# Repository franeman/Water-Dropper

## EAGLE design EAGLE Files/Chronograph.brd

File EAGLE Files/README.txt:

The water dropper uses the same board as the chronograph project. Do not install R2 to use the water dropper.
R3 is not needed for the water dropper but will not effect the circuit should you want to use the chronograph.

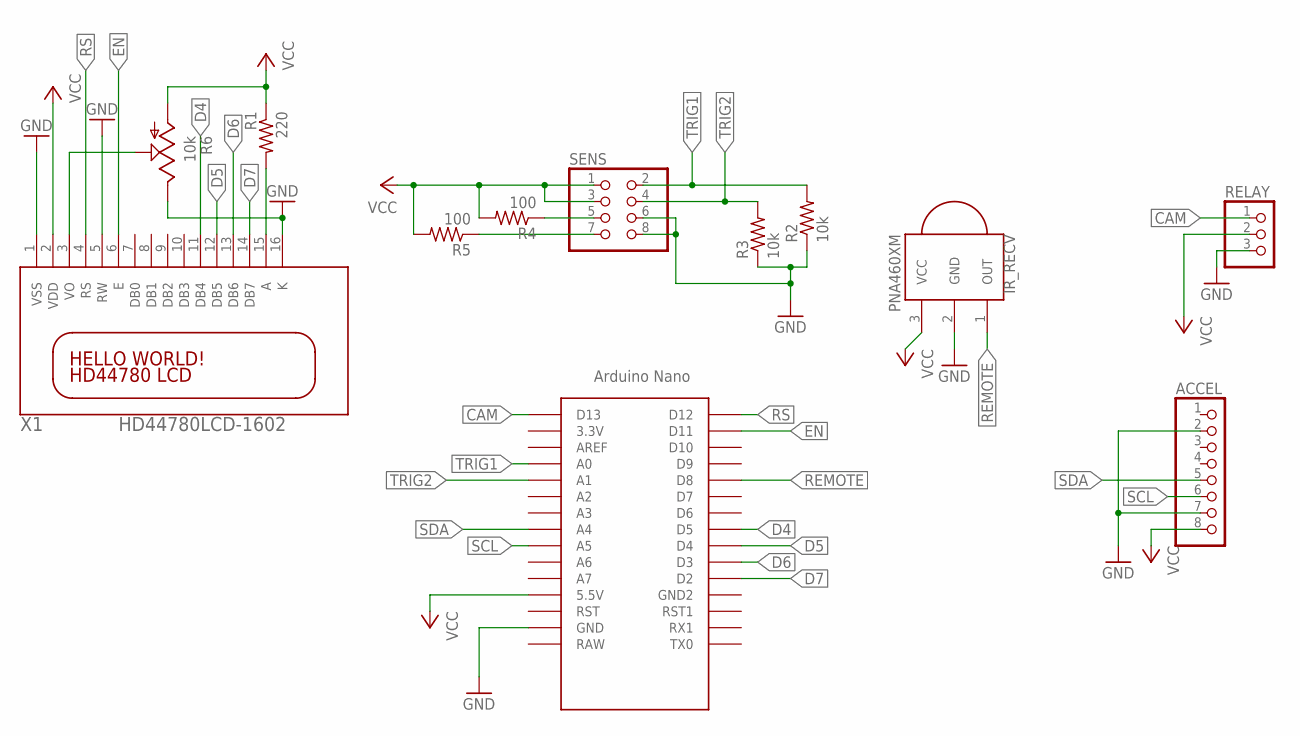
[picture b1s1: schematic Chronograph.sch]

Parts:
ACCEL: PINHD-1X8BIG; 1X08-BIG
IR_RECV: PNA460XM
R1: 220; 0204/7
R2, R3: 10k; 0204/7
R4, R5: 100; 0204/7
R6: 10k; B64Y
RELAY: PINHD-1X3; 1X03
SENS: PINHD-2X4; 2X04
U$1: NANO
X1: HD44780LCD-1602; LCD1602

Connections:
CAM: RELAY.1, U$1.D13
D4: U$1.D5, X1.11 (DB4)
D5: U$1.D4, X1.12 (DB5)
D6: U$1.D3, X1.13 (DB6)
D7: U$1.D2, X1.14 (DB7)
EN: U$1.D11, X1.6 (E)
GRN: ACCEL.2, ACCEL.7, IR_RECV.2 (GND), R2.1, R3.1, R6.E, RELAY.3, SENS.6, SENS.8, U$1.GND, X1.1 (VSS), X1.5 (RW), X1.16 (K)
unnamed: R1.2, X1.15 (A)
unnamed: R5.1, SENS.7
unnamed: R4.1, SENS.5
unnamed: R6.S, X1.3 (VO)
REMOTE: IR_RECV.1 (OUT), U$1.D8
RS: U$1.D12, X1.4 (RS)
SCL: ACCEL.6, U$1.A5
SDA: ACCEL.5, U$1.A4
TRIG1: R2.2, SENS.2, U$1.A0
TRIG2: R3.2, SENS.4, U$1.A1
VCC: ACCEL.8, IR_RECV.3 (VCC), R1.1, R4.2, R5.2, R6.A, RELAY.2, SENS.1, SENS.3, U$1.5V (5.5V), X1.2 (VDD)

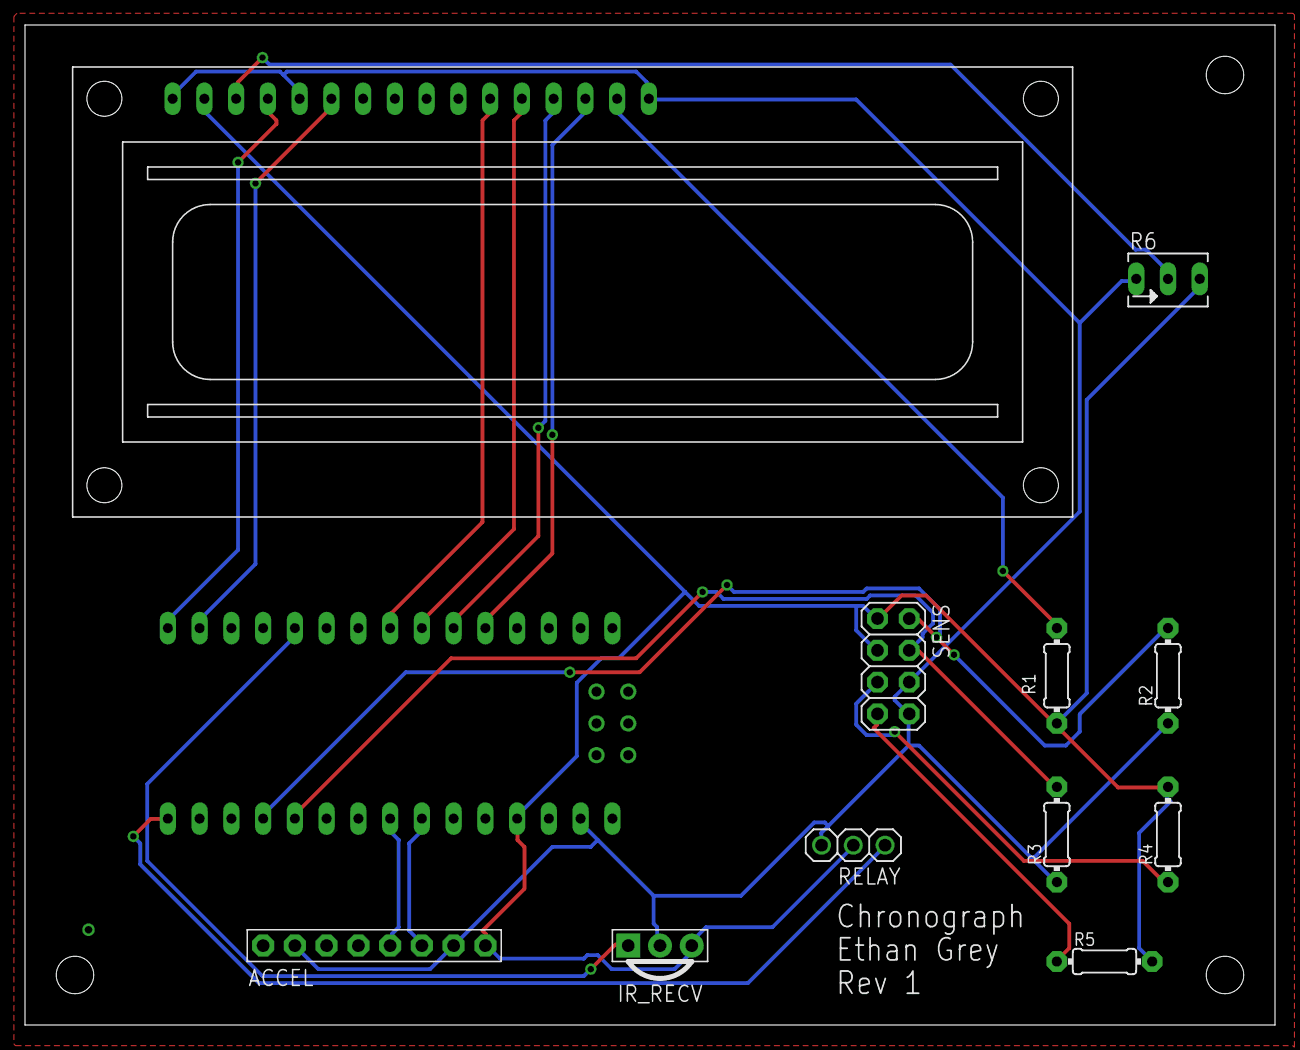
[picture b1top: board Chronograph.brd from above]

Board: 2 copper layers, 100.0 x 80.0 mm, 12 parts (0 on the bottom side), 18 nets.

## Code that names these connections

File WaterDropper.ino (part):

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
// Pin numbers
// Inputs
#define REMOTE 8
// Outputs
#define CAM 13
// Solenoid relay on A0

bool fire = false; // Determines if the dropper is in dropping or options mode
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
void setup() {
  // Inputs
  pinMode(REMOTE,INPUT);
  
  // Outputs
  pinMode(CAM,OUTPUT);
  DDRC |= 0x01; // Set ADC0 (A0) to be a digital output
  
  // IR remote
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    //short trim = 0; // used as an offset 
    
    //float distTarget = 0;   // Distance between end of muzzle to target in ft
    //float distTrig1 = 0;    // Distance between muzzle and trig1 in ft   
    
    if(distTar != -1) // Check Dist Target
      {
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
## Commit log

2018-11-30 Code compiles
2018-11-30 Built atmel studio code
2018-11-30 Added EAGLE files, uses chronograph board. Do NOT install R2!
